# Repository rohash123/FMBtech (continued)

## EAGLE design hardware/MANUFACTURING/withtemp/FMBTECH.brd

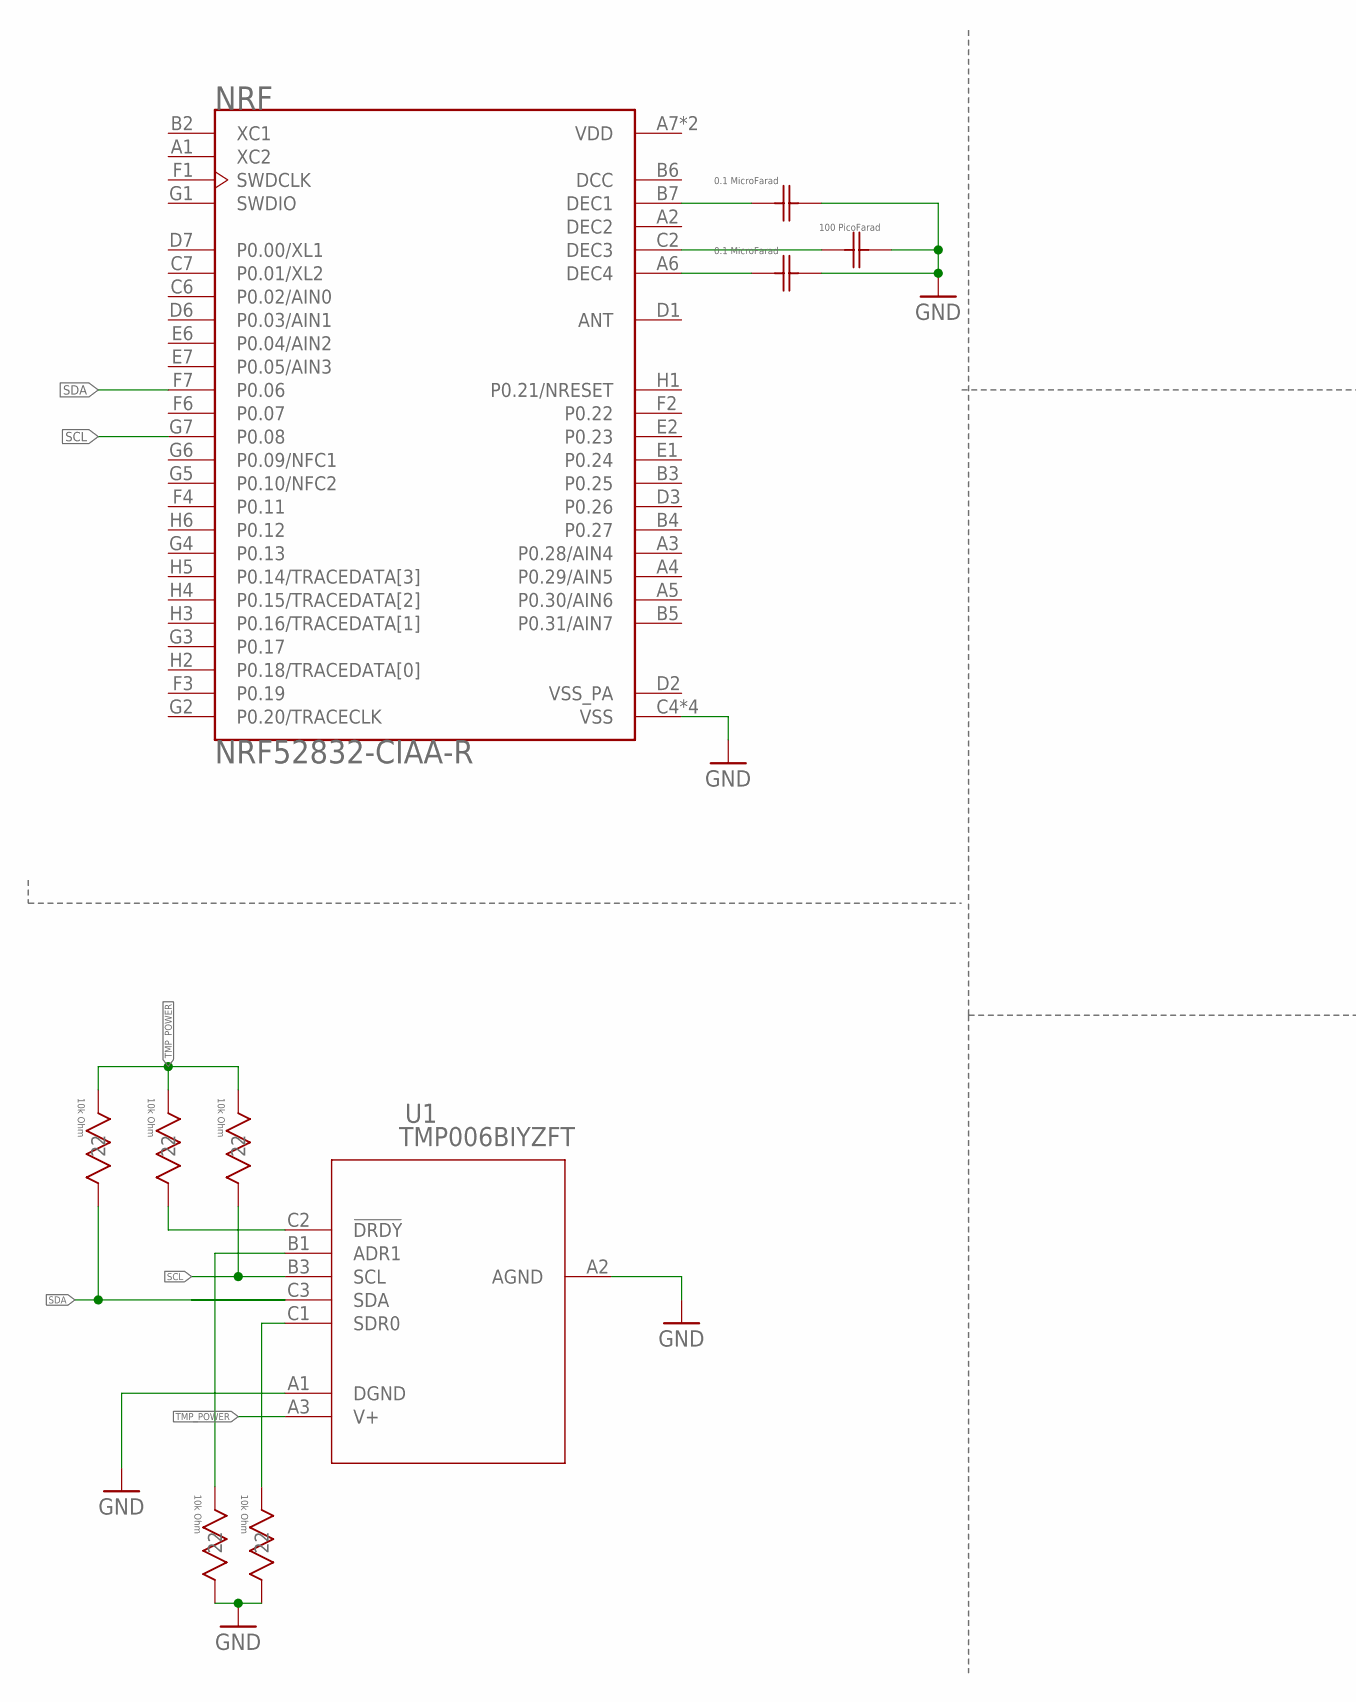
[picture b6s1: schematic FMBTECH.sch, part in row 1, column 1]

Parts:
C1, C2: 02016D104KAT2A; 0201
C3: GRM0335C1E101JA01D; G-033
NRF: NRF52832-CIAA-R; BGA50N40P7X8_300X320X40
R1, R2, R3, R4, R5: RC0402JR-0710KL; RC0402N
U1: TMP006BIYZFT; YZF8

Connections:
DCC: NRF.B6 (DCC)
DEC2: NRF.A2 (DEC2)
GND: C1.2, C2.2, C3.2 (22), NRF.C4 (VSS), NRF.C5 (VSS), NRF.E3 (VSS), NRF.F5 (VSS), R4.1 (11), R5.1 (11), U1.A1 (DGND), U1.A2 (AGND)
unnamed: R5.2 (22), U1.C1 (SDR0)
unnamed: R4.2 (22), U1.B1 (ADR1)
unnamed: R3.1 (11), U1.C2 (!DRDY)
unnamed: C2.1, NRF.A6 (DEC4)
unnamed: C1.1, NRF.B7 (DEC1)
unnamed: C3.1 (11), NRF.C2 (DEC3)
SCL: NRF.G7 (P0.08), R2.1 (11), U1.B3 (SCL)
SDA: NRF.F7 (P0.06), R1.1 (11), U1.C3 (SDA)
TMP_POWER: R1.2 (22), R2.2 (22), R3.2 (22), U1.A3 (V+)
VDD: NRF.A7 (VDD), NRF.H7 (VDD)
VSS_PA: NRF.D2 (VSS_PA)

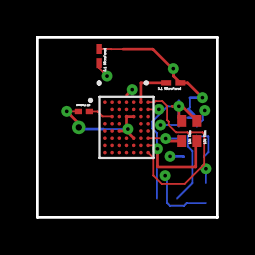
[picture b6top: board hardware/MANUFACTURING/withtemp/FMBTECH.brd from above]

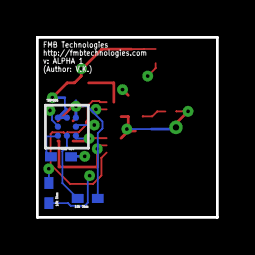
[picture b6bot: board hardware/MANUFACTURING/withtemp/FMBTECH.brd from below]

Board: 6 copper layers, 10.0 x 10.0 mm, 10 parts (4 on the bottom side), 11 nets.

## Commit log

2018-04-16 uploading FMBtechnolgoies files to git for easier versioning
2018-04-18 added silkscreen layer/wrote eagle ulp to make silkscreen layer - 21tplace
2018-04-18 added txt
2018-04-18 remove a.txt
2018-04-25 added arduino code for preliminary observation study -- adjustable sampling rates
2018-04-25 added comments
2018-04-25 working adxl reset fix
2018-04-25 adxl reset timer and formatting
2018-04-25 adjust adxl reset timer and cs
2018-04-25 minor changes adxl reset
2018-04-25 minor changes
2018-04-25 minor fixes
2018-04-25 changed serial output to BIN/formatting
2018-04-26 revert to dec
2018-04-27 fixes to sram reset
2018-04-27 powerctl
2018-04-27 bug fixes
2018-04-29 arora
